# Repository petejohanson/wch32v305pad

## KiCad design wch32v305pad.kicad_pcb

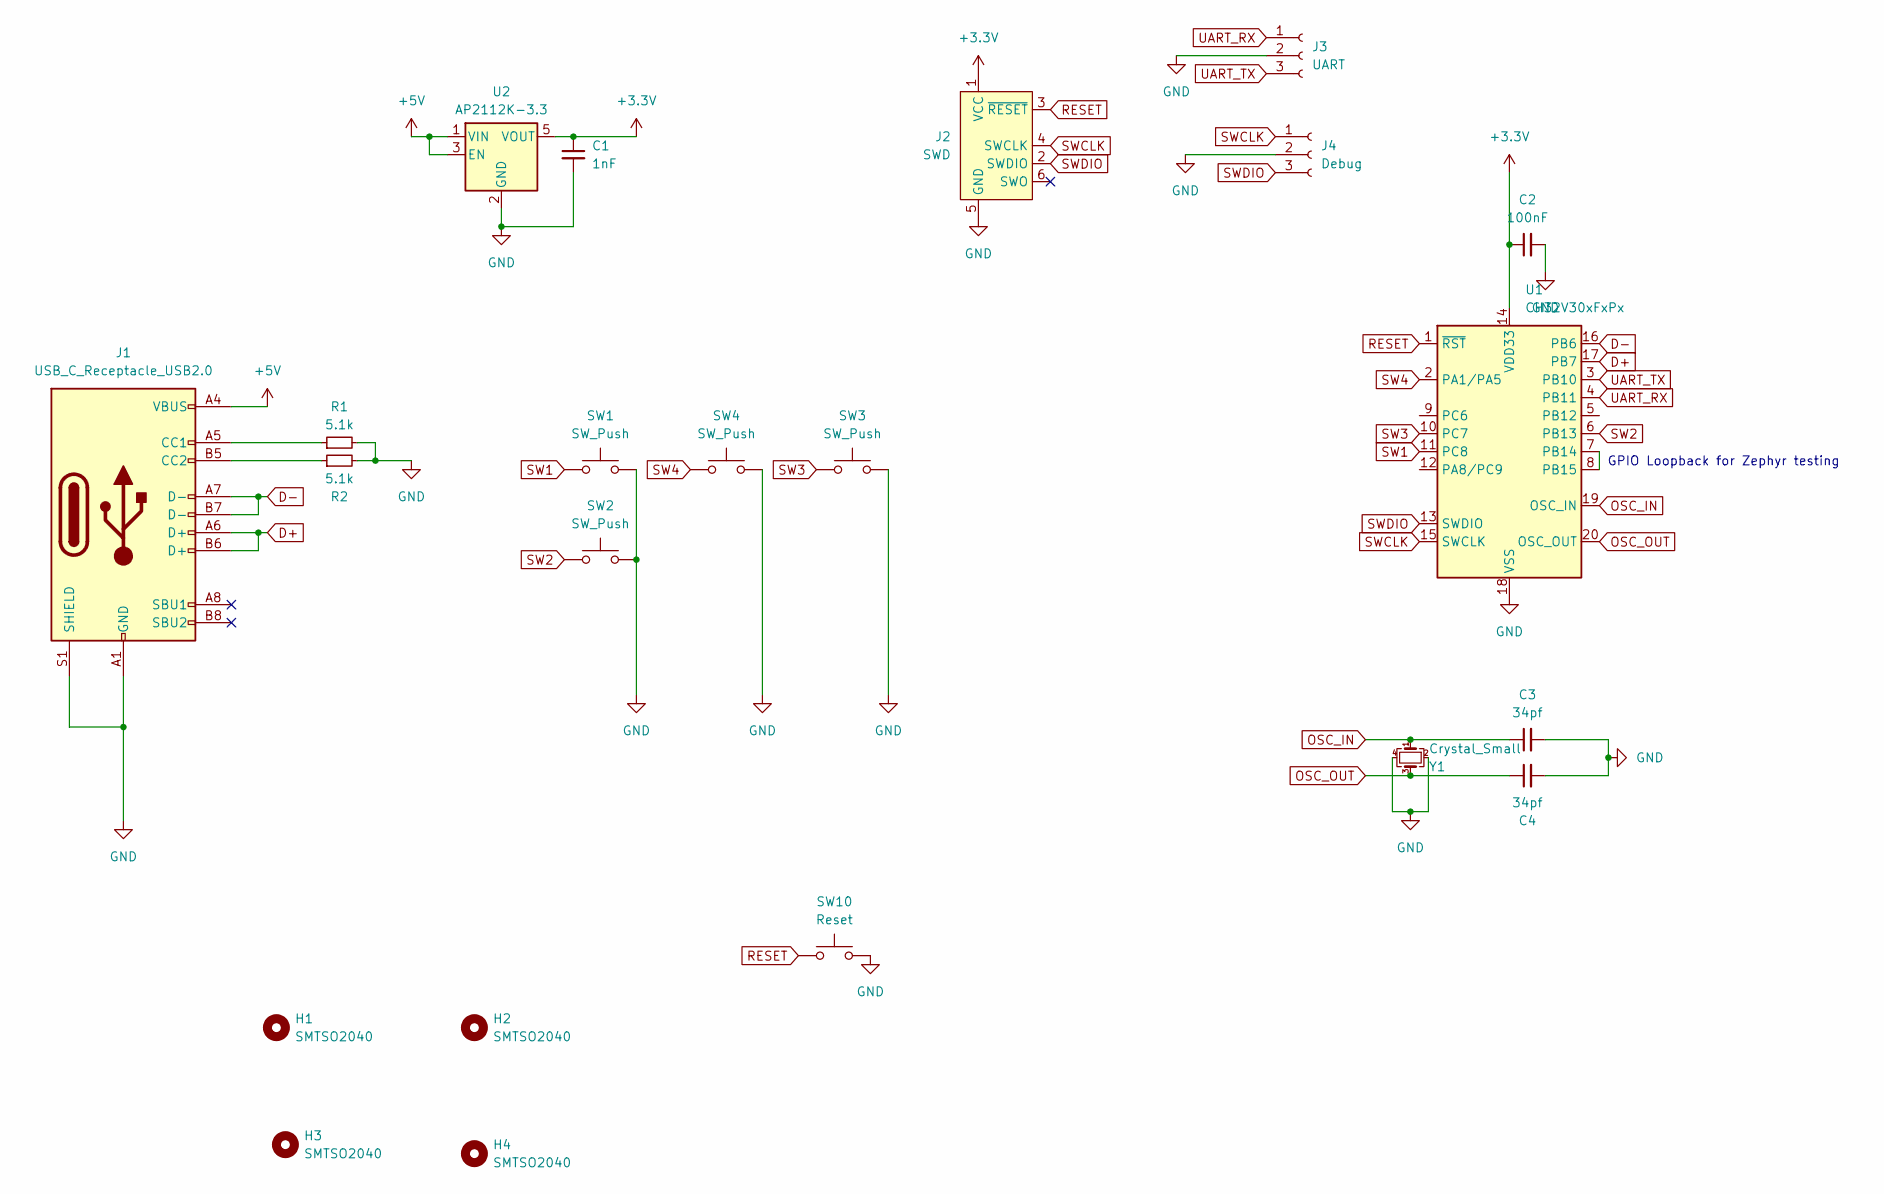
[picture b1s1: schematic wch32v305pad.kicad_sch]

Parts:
C1: 1nF; C_0805_2012Metric; LCSC Part Number C129637
C2: 100nF; C_0805_2012Metric; LCSC Part Number C2169363
C3, C4: 34pf; C_0805_2012Metric_Pad1.18x1.45mm_HandSolder; LCSC Part Number C1816
H1, H2, H3, H4: SMTSO2040; MountingHole_M2_Pad_NonPTH_TopOnly; LCSC Part Number C2916349
J1: USB_C_Receptacle_USB2.0; USB_C_Receptacle_GT-USB-7010; LCSC Part Number C2843967
J2: SWD; Tag-Connect_TC2030-IDC-NL_2x03_P1.27mm_Vertical
J3: UART; JST_SH_SM03B-SRSS-TB_1x03-1MP_P1.00mm_Horizontal; LCSC Part Number C160403
J4: Debug; JST_SH_SM03B-SRSS-TB_1x03-1MP_P1.00mm_Horizontal; LCSC Part Number C160403
R1, R2: 5.1k; R_0805_2012Metric; LCSC Part Number C27834
SW1, SW2, SW3, SW4: SW_Push; SW_MX_1u
SW10: Reset; Panasonic_EVQPUL_EVQPUC; MPN EVQPUC02K; LCSC Part Number C79175
U1: CH32V30xFxPx; TSSOP-20_4.4x6.5mm_P0.65mm; LCSC Part Number C5123443
U2: AP2112K-3.3; SOT-23-5; MPN AP2112K-3.3; LCSC Part Number C3021085
Y1: Crystal_Small; Crystal_SMD_3225-4Pin_3.2x2.5mm_HandSoldering; LCSC Part Number C7464894

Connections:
+3.3V: C1.1, C2.1, J2.1 (VCC), U1.14 (VDD33), U2.5 (VOUT)
+5V: J1.A4 (VBUS), J1.A9 (VBUS), J1.B4 (VBUS), J1.B9 (VBUS), U2.1 (VIN), U2.3 (EN)
D+: J1.A6 (D+), J1.B6 (D+), U1.17 (PB7)
D-: J1.A7 (D-), J1.B7 (D-), U1.16 (PB6)
GND: C1.2, C2.2, C3.2, C4.2, J1.A1 (GND), J1.A12 (GND), J1.B1 (GND), J1.B12 (GND), J1.S1 (SHIELD), J2.5 (GND), J3.2, J4.2, R1.2, R2.2, SW1.2, SW2.2, SW3.1, SW4.1, SW10.1, U1.18 (VSS), U2.2 (GND), Y1.2, Y1.4
unnamed: J1.A5 (CC1), R1.1
unnamed: J1.B5 (CC2), R2.1
unnamed: U1.7 (PB14), U1.8 (PB15)
OSC_IN: C3.1, U1.19 (OSC_IN), Y1.1
OSC_OUT: C4.1, U1.20 (OSC_OUT), Y1.3
RESET: J2.3 (~RESET), SW10.2, U1.1 (~RST)
SW1: SW1.1, U1.11 (PC8)
SW2: SW2.1, U1.6 (PB13)
SW3: SW3.2, U1.10 (PC7)
SW4: SW4.2, U1.2 (PA1/PA5)
SWCLK: J2.4 (SWCLK), J4.1, U1.15 (SWCLK)
SWDIO: J2.2 (SWDIO), J4.3, U1.13 (SWDIO)
UART_RX: J3.1, U1.4 (PB11)
UART_TX: J3.3, U1.3 (PB10)

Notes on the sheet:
GPIO Loopback for Zephyr testing

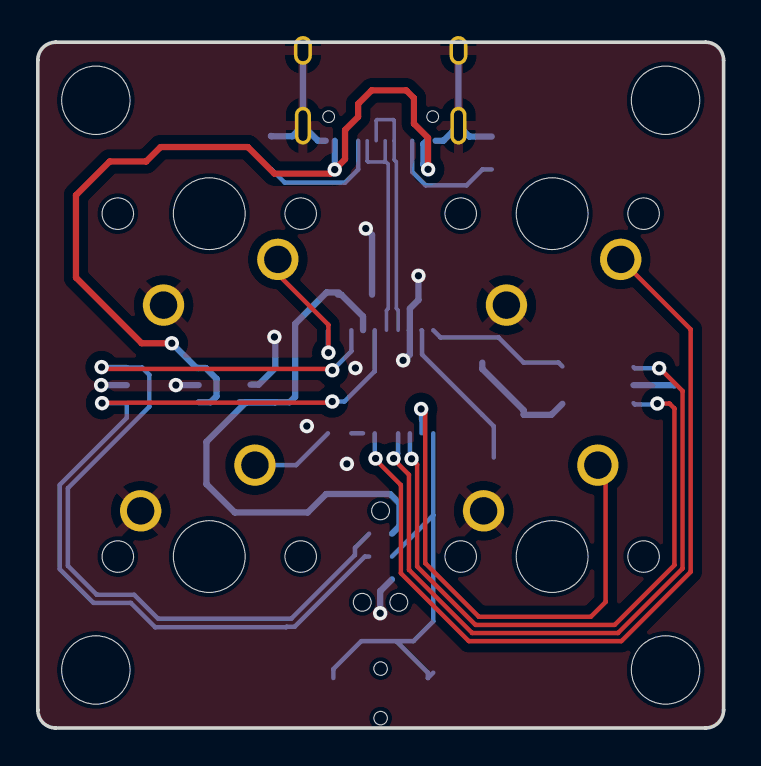
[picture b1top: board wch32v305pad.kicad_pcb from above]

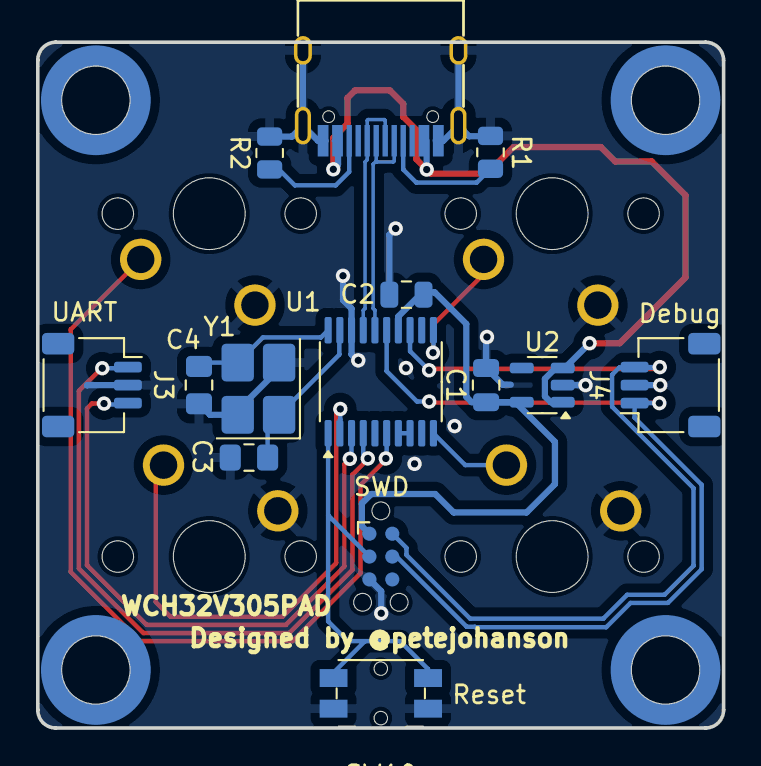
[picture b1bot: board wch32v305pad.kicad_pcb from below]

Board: 2 copper layers, 38.1 x 38.1 mm, 22 parts (18 on the bottom side), 19 nets.

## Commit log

2025-05-22 Refactor to WCH32V305.
2025-05-22 Fix up GHA export.
2025-05-22 Fix step dependency name.
2025-05-22 Fix merged name.
2025-05-22 BOM fixes.
2025-05-22 Routing cleanups, some ignored files.
